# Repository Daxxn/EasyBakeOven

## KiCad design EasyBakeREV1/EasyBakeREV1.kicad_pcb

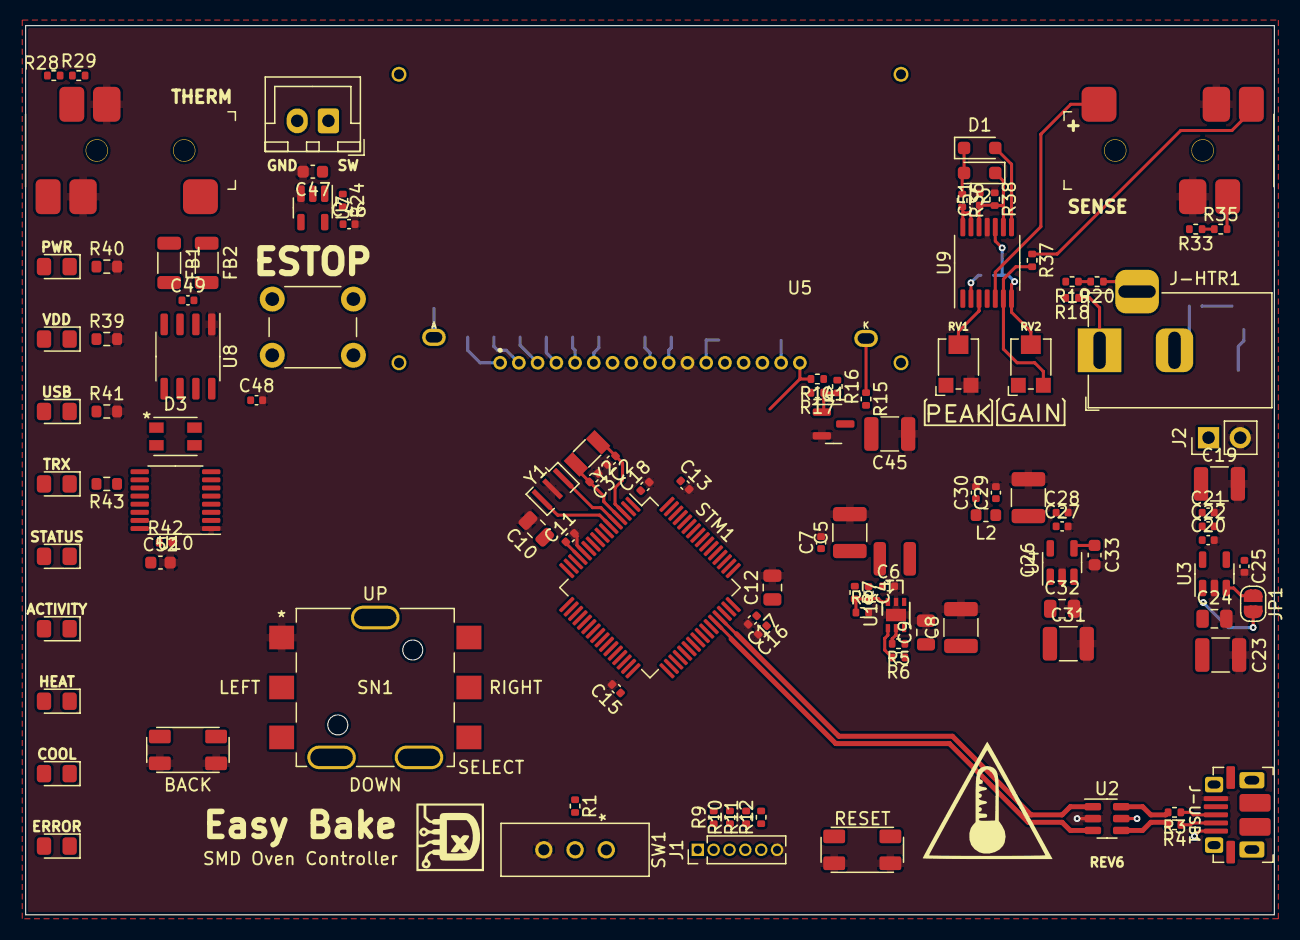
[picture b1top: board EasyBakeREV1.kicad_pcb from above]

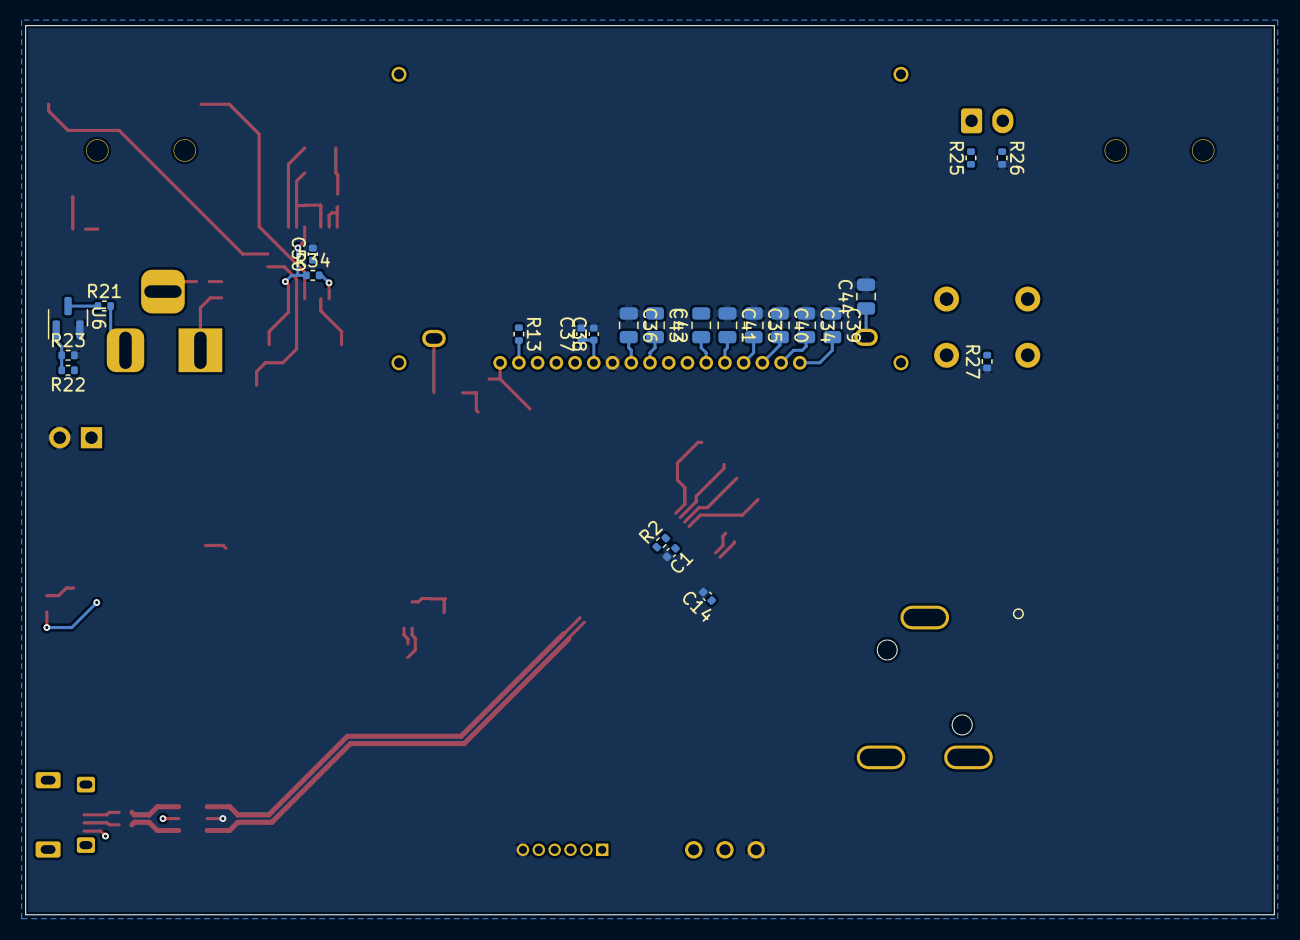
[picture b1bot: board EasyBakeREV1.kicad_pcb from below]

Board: 2 copper layers, 100.0 x 71.2 mm, 137 parts (24 on the bottom side), 106 nets.

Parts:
C1, C6, C7, C13, C14, C15, C16, C17, C18, C20, C21, C22, C27, C28, C29, C30, C37, C38, C46, C48, C50, C51: 100nF; C_0402_1005Metric
C2, C3: 15pF; C_0402_1005Metric
C4: 22pF; C_0402_1005Metric
C5, C8, C19, C23, C26, C31, C45: 10uF; C_1210_3225Metric
C9, C10, C24, C32, C34, C35, C36, C39, C40, C41, C44: 1uF; C_0805_2012Metric
C11, C49: 10nF; C_0402_1005Metric
C12: 4.7uF; C_0805_2012Metric
C25: 470pF; C_0402_1005Metric
C33: 470pF; C_0603_1608Metric
C42, C43: 2.2uF; C_0805_2012Metric
C47: 1uF; C_0603_1608Metric
C52: 100nF; C_0603_1608Metric
D1, D2: General; D_SOD-323_HandSoldering
D3: LED_RGBA; IN-P32TATRGB
D-ACT1: GREEN; LED_0805_2012Metric_Pad1.15x1.40mm_HandSolder
D-COOL1: BLUE; LED_0805_2012Metric_Pad1.15x1.40mm_HandSolder
D-ERR1: RED; LED_0805_2012Metric_Pad1.15x1.40mm_HandSolder
D-HEAT1: ORANGE; LED_0805_2012Metric_Pad1.15x1.40mm_HandSolder
D-STA1: YELLOW; LED_0805_2012Metric_Pad1.15x1.40mm_HandSolder
D-TX1: YELLOW; LED_0805_2012Metric_Pad1.15x1.40mm_HandSolder
D-USB1: YELLOW; LED_0805_2012Metric_Pad1.15x1.40mm_HandSolder
D-VCC1: YELLOW; LED_0805_2012Metric_Pad1.15x1.40mm_HandSolder
D-VDD1: YELLOW; LED_0805_2012Metric_Pad1.15x1.40mm_HandSolder
FB1, FB2: FerriteBead; L_1206_3216Metric
J1: SWD; PinHeader_1x06_P1.27mm_Vertical
J2: PWR; PinHeader_1x02_P2.54mm_Vertical
J-ESTOP1: Conn_01x02; JST_XH_B2B-XH-A_1x02_P2.50mm_Vertical
J-HTR1: Barrel_Jack_Switch; BarrelJack_Horizontal
J-SENSE1: SJ-43515RS-SMT-TR
J-THERM1: SJ-43515RS-SMT-TR
J-USB1: USB_B_Micro; USB-10103594
JP1: USB-PWR-EN; SolderJumper-2_P1.3mm_Open_RoundedPad1.0x1.5mm
L1: 2.2uF; LQH3NPN
L2: 100nH; L_0603_1608Metric
Q1: SQ2310ES_SOT23; SOT-23
R1, R2, R5, R6, R13, R14, R16, R19, R23, R24, R27, R28, R33, R36, R38: 10K; R_0402_1005Metric
R3, R4, R9, R10, R11, R12, R25, R26: 22; R_0402_1005Metric
R7: 430K; R_0402_1005Metric
R8: 100K; R_0402_1005Metric
R15, R18, R20, R21, R22, R29, R34, R35: 100; R_0402_1005Metric
R17, R37: 1K; R_0402_1005Metric
R39, R43: 330; R_0603_1608Metric
R40, R41: 1K; R_0603_1608Metric
R42: 2K; R_0402_1005Metric
RV1: 10K; Bourns_TC33X
RV2: 50K; Bourns_TC33X
SN1: JS5208
STM1: STM32F303RCT6TR; LQFP-64_10x10mm_P0.5mm
SW1: BOOT; EG1218
SW-ESTOP1: SW_SPST; SW_PUSH_6mm_H8mm
SW-M-BK1: SW_SPST; TL3365AF180QG
SW-RESET1: SW_SPST; TL3365AF180QG
U1: AP3401; DFN-6-1EP_2x2mm_P0.65mm_EP1x1.6mm
U2: USBLC6-2SC6; SOT-23-6
U3: MIC5219-5.0YM5; SOT-23-5
U4: MIC5219-3.3YM5; SOT-23-5
U5: NHD-C12832A1Z
U6: SQ2310ES_SOT23; SOT-23
U7: SN74LVC1G32; SOT-23-5
U8: MAX31855_SO8; SO-8_3.9x4.9mm_P1.27mm
U9: LM324; TSSOP-14_4.4x5mm_P0.65mm
U10: STP08CP05; TSSOP-16_4.4x5mm_P0.65mm
Y1: 16MHz; Resonator_SMD_3Pin_3.0x1.1mm
Y2: 32.7KHz; Crystal_SMD_3215-2Pin_3.2x1.5mm

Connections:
/CURR-BIAS: R34.2, STM1.15 (ADC1-IN2), U9.1, U9.2 (-)
/CURR-PEAK: R36.2, STM1.17 (COMP2-IN+), U9.13 (-), U9.14
/CURR-SENSE: R34.1, RV2.2, STM1.14 (ADC1-IN1), U9.7, U9.10 (+)
/CURR-SENSE-SW: R33.1, R35.1, STM1.16 (PA2)
/DISP-A0: STM1.24 (PC4), U5.15 (A0)
/DISP-BK-PWM: R17.2, STM1.22 (TIM3-CH1)
/DISP-~CS: R14.2, STM1.20 (PA4), U5.17 (~CS)
/DISP-~RESET: R13.2, STM1.25 (PC5), U5.16 (~RESET)
/ESTOP-SW: STM1.39 (PC8), U7.4
/HTR-PWM: R22.1, STM1.27 (TIM3-CH4)
/HTR-SW: R19.1, R20.2, STM1.26 (PB0)
/IND-LE: STM1.50 (PA15), U10.4 (LE)
/IND-OE: STM1.54 (PD2), U10.13 (~OE)
/Indicators/IND-ACT: D-ACT1.1 (K), U10.9 (OUT4)
/Indicators/IND-BLUE: D3.4 (A), U10.5 (OUT0)
/Indicators/IND-COOL: D-COOL1.1 (K), U10.11 (OUT6)
/Indicators/IND-ERR: D-ERR1.1 (K), U10.12 (OUT7)
/Indicators/IND-GREEN: D3.3 (BK), U10.6 (OUT1)
/Indicators/IND-HEAT: D-HEAT1.1 (K), U10.10 (OUT5)
/Indicators/IND-RED: D3.1 (RK), U10.7 (OUT2)
/Indicators/IND-STATUS: D-STA1.1 (K), U10.8 (OUT3)
/MAIN-PG: R5.2, U1.2 (PG)
/MENU-BACK: STM1.29 (PB10), SW-M-BK1.1 (A)
/MENU-DOWN: SN1.6 (DOWN), STM1.36 (PB15)
/MENU-LEFT: SN1.2 (LEFT), STM1.33 (PB12)
/MENU-RIGHT: SN1.5 (RIGHT), STM1.35 (PB14)
/MENU-SELECT: SN1.3 (PUSH), STM1.34 (PB13)
/MENU-UP: SN1.4 (UP), STM1.30 (PB11)
/SWCLK: R10.2, STM1.49 (SWCLK_JTCK)
/SWDIO: R11.2, STM1.46 (SWDIO_JTMS)
/SWO: R12.2, STM1.55 (JTDO_TRACESWO)
/THERM-SW: R29.2, STM1.18 (PF4)
/THERM-~CS: STM1.40 (PC9), U8.6 (~CS)
/TX-IND: R43.1, STM1.38 (TIM3-CH2)
/USBIN+: R3.2, STM1.45 (USB-D+), U2.1 (I/O1), U2.6 (I/O1)
/USBIN-: R4.2, STM1.44 (USB-D-), U2.3 (I/O2), U2.4 (I/O2)
DISP-SPI-COPI: STM1.23 (SPI1-COPI), U5.13 (SDA)
DISP-SPI-SCLK: STM1.21 (SPI1-SCK), U5.14 (SCLK)
GND: C1.2, C2.2, C3.1, C5.2, C6.2, C7.2, C8.2, C9.2, C10.2, C11.2, C12.2, C13.2, C14.2, C15.2, C16.2, C17.2, C18.2, C19.2, C20.2, C21.2, C22.2, C23.2, C24.2, C25.2, C26.2, C27.2, C28.2, C29.2, C30.2, C31.2, C32.2, C33.2, C34.1, C35.1, C36.1, C37.2, C38.2, C39.1, C40.1, C41.1, C44.2, C45.1, C46.2, C47.2, C48.2, C50.2, C51.2, C52.2, J1.6, J2.2, J-SENSE1.R1, J-SENSE1.R2, J-THERM1.R1, J-THERM1.R2, J-USB1.5 (GND), Q1.2 (S), R8.2, R23.2, R26.2, R27.1, R38.1, R39.2, R40.2, R41.2, R42.2, RV1.3, SN1.1 (COM), STM1.12 (GNDA), STM1.31 (GND), STM1.47 (GND), STM1.63 (GND), SW1.3 (C), SW-M-BK1.2 (B), SW-RESET1.1 (A), U1.5 (GND), U1.7 (GND), U2.2 (GND), U3.2 (GND), U4.2 (GND), U5.11 (GND), U6.2 (S), U7.3, U8.1 (GND), U9.11 (V-), U10.1 (GND), Y1.2
unnamed: C47.1, R24.1, R25.1, U7.1
unnamed: D1.2 (A), U9.8
unnamed: D1.1 (K), D2.2 (A), R36.1
unnamed: C51.1, D2.1 (K), R38.2, U9.9 (-), U9.12 (+)
unnamed: D-TX1.1 (K), R43.2
unnamed: D-USB1.1 (K), R41.1
unnamed: D-VCC1.1 (K), R40.1
unnamed: D-VDD1.1 (K), R39.1
unnamed: FB1.2, J-THERM1.S
unnamed: FB2.2, J-THERM1.T
unnamed: J1.2, R9.1
unnamed: J1.3, R10.1
unnamed: J1.4, R11.1
unnamed: J1.5, R12.1
unnamed: J-ESTOP1.1, R25.2
unnamed: J-ESTOP1.2, R26.1
unnamed: J-HTR1.1, R18.1
unnamed: J-HTR1.2, R21.2
unnamed: J-HTR1.3, R20.1
unnamed: J-SENSE1.S, R37.1
unnamed: J-SENSE1.SW, R35.2
unnamed: J-THERM1.SW, R28.1, R29.1
unnamed: J-USB1.3 (D+), R3.1
unnamed: J-USB1.2 (D-), R4.1
unnamed: JP1.1 (A), U3.3 (EN)
unnamed: C45.2, Q1.3 (D), R15.2
unnamed: Q1.1 (G), R16.2, R17.1
unnamed: R1.1, STM1.60 (BOOT0)
unnamed: STM1.5 (OSC-IN), Y1.1
unnamed: STM1.6 (OSC-OUT), Y1.3
unnamed: C2.1, STM1.3 (OSC32-IN), Y2.2
unnamed: C3.2, STM1.4 (OSC32-OUT), Y2.1
unnamed: R1.2, SW1.2 (B)
unnamed: R27.2, SW-ESTOP1.1 (A), U7.2
unnamed: R6.2, U1.1 (EN)
unnamed: C4.2, R7.2, R8.1, U1.6 (FB)
unnamed: L1.1, U1.4 (LX)
unnamed: C25.1, U3.4 (BP)
unnamed: C33.1, U4.4 (BP)
unnamed: C26.1, C27.1, C28.1, C29.1, L2.1, U4.5 (OUT)
unnamed: C43.1, U5.8 (C1+)
unnamed: C43.2, U5.9 (C1-)
unnamed: C42.2, U5.7 (C2+)
unnamed: C42.1, U5.6 (C2-)
unnamed: R15.1, U5.K (LED-)
unnamed: C39.2, U5.1 (V_{0})
unnamed: C34.2, U5.2 (V_{1})
unnamed: C40.2, U5.3 (V_{2})
unnamed: C35.2, U5.4 (V_{3})
unnamed: C41.2, U5.5 (V_{4})
unnamed: C36.2, U5.10 (V_{OUT})
unnamed: R21.1, U6.3 (D)
unnamed: R22.2, R23.1, U6.1 (G)
unnamed: C49.1, FB1.1, U8.3 (T+)
unnamed: C49.2, FB2.1, U8.2 (T-)
unnamed: RV1.2, U9.3 (+)
unnamed: J-SENSE1.T, U9.5 (+)
unnamed: R37.2, RV2.3, U9.6 (-)
unnamed: R42.1, U10.15 (R-EXT)
RESET: C1.1, R2.2, R9.2, STM1.7 (~RESET), SW-RESET1.2 (B)
SPI-CIPO: STM1.52 (SPI3-CIPO), U8.7 (CIPO)
SPI-COPI: STM1.53 (SPI3-COPI), U10.2 (SDI)
SPI-SCLK: STM1.51 (SPI3-SCK), U8.5 (SCLK), U10.3 (CLK)
VBUS: C8.1, C9.1, C23.1, C24.1, D-USB1.2 (A), J-USB1.1 (VBUS), JP1.2 (B), R5.1, R6.1, U1.3 (VIN), U2.5 (VBUS), U3.1 (IN)
VCC: C19.1, C20.1, C21.1, C22.1, C31.1, C32.1, C46.1, C50.1, D3.2 (GK), D-ACT1.2 (A), D-COOL1.2 (A), D-ERR1.2 (A), D-HEAT1.2 (A), D-STA1.2 (A), D-TX1.2 (A), D-VCC1.2 (A), J2.1, R18.2, R19.2, R24.2, R28.2, R33.2, RV1.1, SW-ESTOP1.2 (B), U3.5 (OUT), U4.1 (IN), U4.3 (EN), U7.5, U9.4 (V+)
VDD: C4.1, C5.1, C6.1, C7.1, C12.1, C13.1, C14.1, C15.1, C16.1, C17.1, C18.1, C37.1, C38.1, C44.1, C48.1, C52.1, D-VDD1.2 (A), J1.1, L1.2, R2.1, R7.1, R13.1, R14.1, R16.1, STM1.1 (VBAT), STM1.19 (VDD), STM1.32 (VDD), STM1.48 (VDD), STM1.64 (VDD), SW1.1 (A), U5.12 (VCC), U5.A (LED+), U8.4 (VCC), U10.16 (VDD)
VDDA: C10.1, C11.1, C30.1, L2.2, STM1.13 (VDDA)

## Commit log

2023-01-13 REV3 - Reorganize MC pinouts and add LED driver (WIP)
2023-03-19 Update to KiCad 7
2023-04-01 Start of firmware for REV4
2023-04-02 NOT programming. Going to rework board...again
2023-04-06 Change main pwr to 3.3 due to USB issues
2023-04-06 Replaced MCU - started layout
2023-04-06 Add license
2023-04-07 Rearrange footprints and start layout
